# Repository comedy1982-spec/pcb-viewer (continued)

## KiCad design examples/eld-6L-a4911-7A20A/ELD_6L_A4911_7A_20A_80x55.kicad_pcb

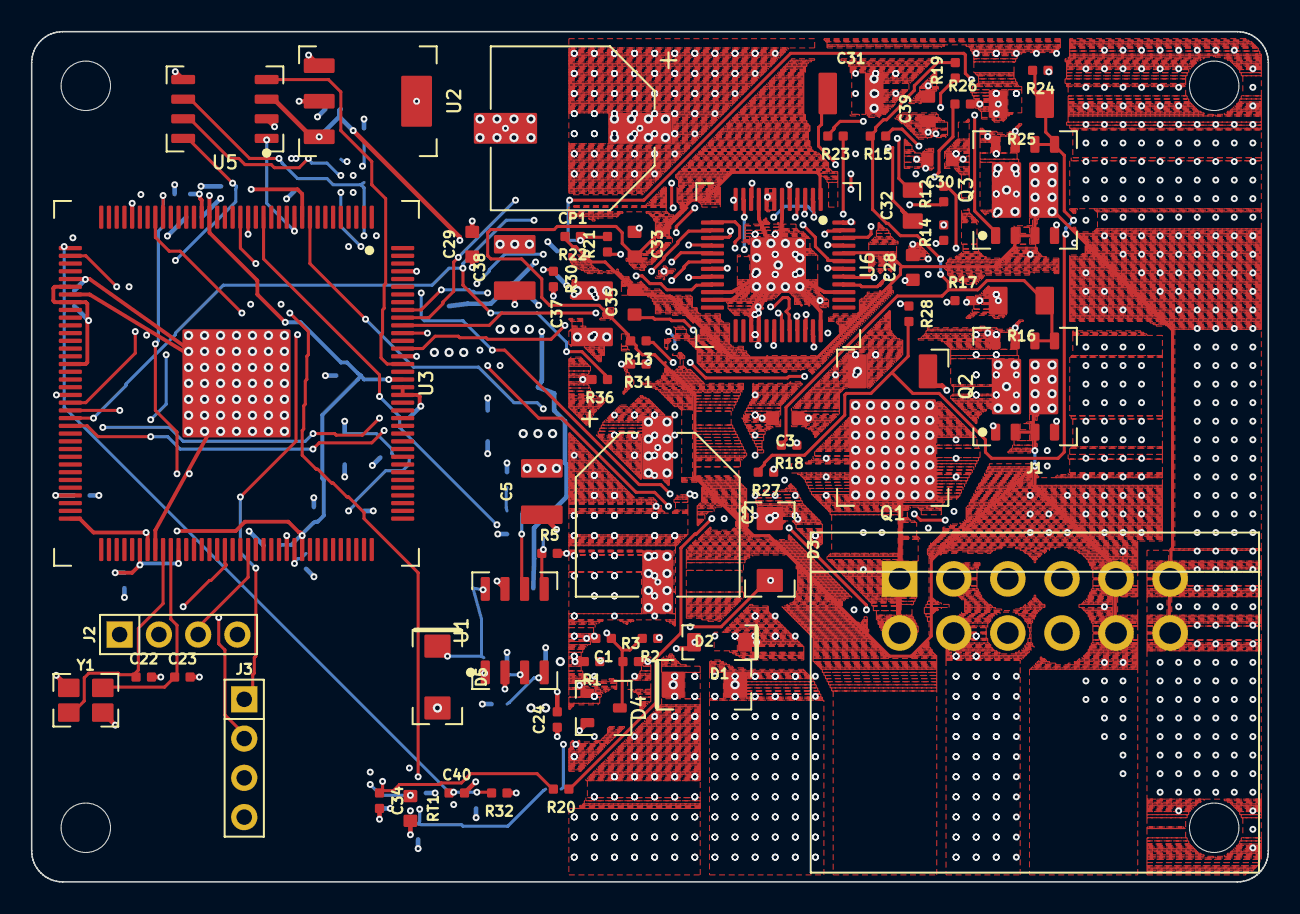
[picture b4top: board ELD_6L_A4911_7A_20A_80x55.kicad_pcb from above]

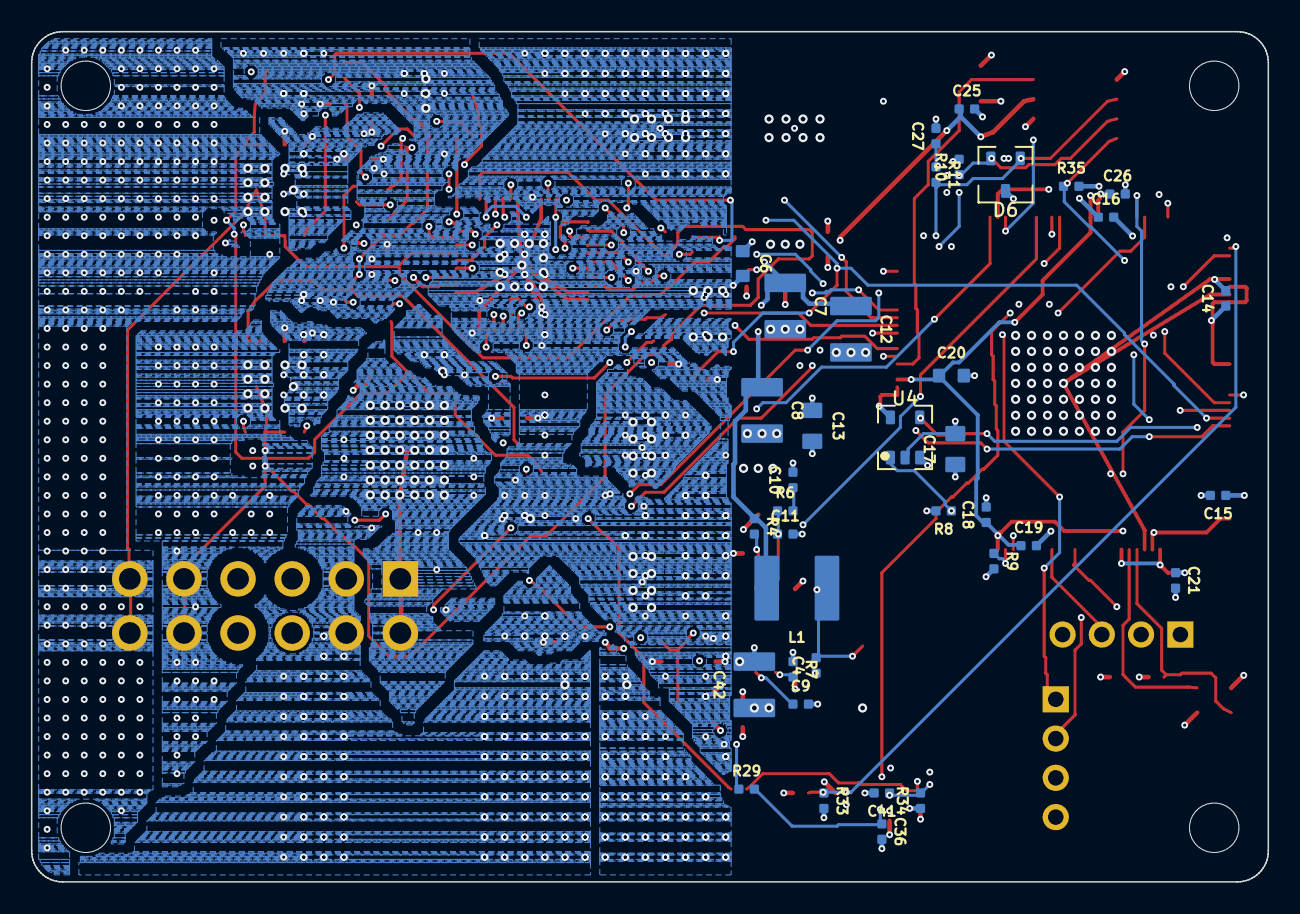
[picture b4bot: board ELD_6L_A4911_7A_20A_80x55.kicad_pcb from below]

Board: 6 copper layers, 80.0 x 55.0 mm, 104 parts (37 on the bottom side), 73 nets.

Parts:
C1, C9: 10nF; 0402
C2: 470µF; CP-SMD-10x10
C3, C6, C28, C29, C30, C39: 100nF; 0603
C4, C14, C15, C16, C18, C19, C21, C24, C25, C26, C40, C41: 100nF; 0402
C5, C12, C42: 10µF; 1210
C7, C8, C31: 22µF; 1210
C10: 3.3nF; 0402
C11: 47pF; 0402
C13, C17: 10µF; 0805
C20: 470nF; 0603
C22, C23: 12pF; 0402
C27: 4.7nF; 0402
C32: 470nF; 0805
C33, C35: 68nF; 0603
C34, C36: 1nF; 0402
C37, C38: 2.2µF; 1210
CP1: 470µF; CP-SMD-10x10
D1: BZT52C12; SOD-123
D2: SMAJ15A; SMA
D3: SMAJ15CA; SMA
D4: BAT54S; SOT-23
D5: MBRA340T3G; SMA
D6: PESD1CAN; SOT-23
H1, H2, H3, H4: MountingHole
J1: ECU; MX150-2x6-RA
J2: DAP; HDR-1x4
J3: UART; HDR-1x4
L1: 10µH; IND-5x5
Q1: SQD50P04-09L; TO-252
Q2, Q3: IAUC60N04S6N050H; TDSON-8-2FET
R1, R3, R5, R8, R9, R13, R15, R22, R24, R30, R31, R34, R35, R36: 10kΩ; 0402
R2: 33kΩ; 0402
R4: 52.3kΩ; 0402
R6: 76.8kΩ; 0402
R7, R32: 100kΩ; 0402
R10, R11: 60.4Ω; 0402
R12, R14, R21, R23: 10Ω; 0402
R16, R25: 2mΩ; 1206
R17, R18, R19, R26, R27, R28: 0Ω; 0402
R20, R29: 1kΩ; 0402
R33: 22kΩ; 0402
RT1: NTC 10k; 0603
U1: TPS54331; SOIC-8
U2: AMS1117-3.3; SOT-223
U3: TC364DP; TQFP-144
U4: TPS3823-33; SOT-23-5
U5: TLE9251V; SOIC-8
U6: A4911; QFP-48-EP-7x7-P0.5
Y1: 20MHz; XTAL-3225

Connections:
+3V3: C13.1, C14.1, C15.1, C16.1, C17.1, C21.1, C24.1, C26.1, D4.2 (K2), J2.1 (3V3), J3.4 (3V3), R8.2, R9.2, R30.2, R34.1, R35.2, U2.2 (VOUT), U2.4 (VOUT), U3.23 (VEXT), U3.42 (VAREF1), U3.44 (VDDM), U3.52 (VEVRSB), U3.69 (VEXT), U3.78 (VEXT), U3.83 (VEXT), U3.125 (VEXT), U3.126 (VDDP3), U4.3 (MR), U4.5 (VDD), U5.5 (VIO)
+5V: C7.1, C8.1, C12.1, C25.1, L1.2, R4.1, U2.3 (VIN), U5.3 (VCC)
+12V: C2.1, C3.1, C5.1, C6.1, C29.1, C30.1, C37.1, C38.1, C39.1, C42.1, CP1.1, D1.1 (K), D2.1 (K), Q1.3 (S), Q2.7 (BAT), Q2.8 (BAT), Q2.9 (BAT), Q3.7 (BAT), Q3.8 (BAT), Q3.9 (BAT), R7.1, R32.1, U1.2 (VIN), U6.7 (VBB), U6.8 (VBRG)
BUCK_BOOT: C4.1, U1.1 (BOOT)
BUCK_COMP: C11.1, R6.1, U1.6 (COMP)
BUCK_EN: R7.2, U1.3 (EN)
BUCK_FB: R4.2, R5.1, U1.5 (VSENSE)
BUCK_RC: C10.1, R6.2
BUCK_SS: C9.1, U1.4 (SS)
BUCK_SW: C4.2, D5.1 (K), L1.1, U1.8 (PH)
CANH: D6.2 (CANH), J1.4 (CAN_H), R10.1, U5.7 (CANH)
CANL: D6.1 (CANL), J1.10 (CAN_L), R11.2, U5.6 (CANL)
CAN_RX: U3.129 (P13.1), U5.4 (RxD)
CAN_SPLIT: C27.1, R10.2, R11.1
CAN_STB: R35.1, U3.57 (P33.1), U5.8 (STB)
CAN_TX: U3.11 (P00.0), U5.1 (TxD)
DBG_RX: J3.2 (RX), U3.17 (P00.6)
DBG_TX: J3.1 (TX), U3.18 (P00.7)
ESR0: R9.1, U3.98 (ESR0)
GND: C1.2, C2.2, C3.2, C5.2, C6.2, C7.2, C8.2, C9.2, C10.2, C11.2, C12.2, C13.2, C14.2, C15.2, C16.2, C17.2, C18.2, C19.2, C20.2, C21.2, C22.2, C23.2, C24.2, C25.2, C26.2, C27.2, C28.2, C29.2, C30.2, C31.2, C34.2, C36.2, C37.2, C38.2, C39.2, C40.2, C41.2, C42.2, CP1.2, D2.2 (A), D3.1 (A1), D4.1 (A1), D5.2 (A), D6.3 (GND), J1.2 (GND), J1.8 (GND), J2.4 (GND), J3.3 (GND), R1.2, R3.2, R5.2, R16.2, R17.2, R25.2, R26.2, R31.2, R33.2, R36.2, RT1.2, U1.7 (GND), U2.1 (GND), U3.41 (VAGND1), U3.43 (VSSM), U3.80 (VSS), U3.145 (VSS (노출 패드)), U4.2 (GND), U5.2 (GND), U6.6 (GND), U6.9 (GND), U6.22 (HC), U6.23 (LC), U6.27 (CS3P), U6.28 (CS3M), U6.36 (LSSC), U6.39 (SC), U6.49 (PAD), Y1.2, Y1.4
HB_A: C33.2, J1.5 (ELD+), J1.11 (ELD+), Q2.2 (PH), Q2.3 (PH), Q2.10 (PH), R13.2, U6.1 (SA)
HB_A_HG: Q2.1 (G_HS), R12.2, R13.1
HB_A_HO: R12.1, U6.48 (GHA)
HB_A_LG: Q2.4 (G_LS), R14.2, R15.1
HB_A_LO: R14.1, U6.47 (GLA)
HB_A_LSS: R19.1, U6.46 (LSSA)
HB_A_SNS: Q2.5 (GND), Q2.6 (GND), R15.2, R16.1, R18.2, R19.2
HB_A_SNSM: R17.1, U6.34 (CS1M)
HB_A_SNSP: R18.1, U6.33 (CS1P)
HB_A_VB: C33.1, U6.2 (CA)
HB_B: C35.2, J1.6 (ELD−), J1.12 (ELD−), Q3.2 (PH), Q3.3 (PH), Q3.10 (PH), R22.2, U6.44 (SB)
HB_B_HG: Q3.1 (G_HS), R21.2, R22.1
HB_B_HO: R21.1, U6.43 (GHB)
HB_B_LG: Q3.4 (G_LS), R23.2, R24.1
HB_B_LO: R23.1, U6.42 (GLB)
HB_B_LSS: R28.1, U6.41 (LSSB)
HB_B_SNS: Q3.5 (GND), Q3.6 (GND), R24.2, R25.1, R27.2, R28.2
HB_B_SNSM: R26.1, U6.31 (CS2M)
HB_B_SNSP: R27.1, U6.30 (CS2P)
HB_B_VB: C35.1, U6.45 (CB)
HB_CC_UNUSED: C28.1, U6.40 (CC)
HB_CP1: C32.1, U6.4 (CP1)
HB_CP2: C32.2, U6.5 (CP2)
HB_DIAG: R30.1, U3.141 (P10.2), U6.17 (DIAG)
HB_EN: R31.1, U3.58 (P33.2), U6.11 (ENABLE)
HB_INH_A: U3.131 (P13.3), U6.18 (HA)
HB_INH_B: U3.130 (P13.2), U6.20 (HB)
HB_INL_A: U3.9 (P02.8), U6.19 (LA)
HB_INL_B: U3.136 (P11.8), U6.21 (LB)
HB_ISNS_A: C34.1, R20.2, U3.28 (AN35)
HB_ISNS_A_AMP: R20.1, U6.35 (CS1O)
HB_ISNS_B: C36.1, R29.2, U3.29 (AN34)
HB_ISNS_B_AMP: R29.1, U6.32 (CS2O)
HB_ISNS_OOS: U3.32 (AN28), U6.10 (OOS)
HB_RESETN: R36.1, U3.59 (P33.3), U6.12 (RESETn)
HB_SCK: U3.134 (P11.6), U6.14 (SCK)
HB_SDI: U3.135 (P11.9), U6.15 (SDI)
HB_SDO: U3.133 (P11.3), U6.16 (SDO)
HB_STRN: U3.60 (P33.4), U6.13 (STRn)
HB_VREG: C31.1, U6.3 (VREG)
IGN_DET: C1.1, D4.3 (K1/A2), R2.2, R3.1, U3.15 (P00.4)
IGN_IN: D3.2 (A2), J1.3 (IGN), R2.1
PORST: R8.1, U3.97 (PORST), U4.1 (RESET)
TCK: J2.3 (TCK), U3.92 (TCK)
TEMP: C41.1, R34.2, RT1.1, U3.38 (AN20)
TMS: J2.2 (TMS), U3.89 (TMS)
VDD: C18.1, C19.1, C20.1, U3.10 (VDD), U3.22 (VDD), U3.72 (VDD), U3.79 (VDD), U3.99 (VDD), U3.127 (VDD)
VIN_PG: D1.2 (A), Q1.1 (G), R1.1
VIN_RAW: J1.1 (BAT), J1.7 (BAT), Q1.2 (D)
VMON: C40.1, R32.2, R33.1, U3.37 (AN21)
WDI: U3.56 (P33.0), U4.4 (WDI)
XTAL1: C22.1, U3.81 (XTAL1), Y1.1
XTAL2: C23.1, U3.82 (XTAL2), Y1.3
